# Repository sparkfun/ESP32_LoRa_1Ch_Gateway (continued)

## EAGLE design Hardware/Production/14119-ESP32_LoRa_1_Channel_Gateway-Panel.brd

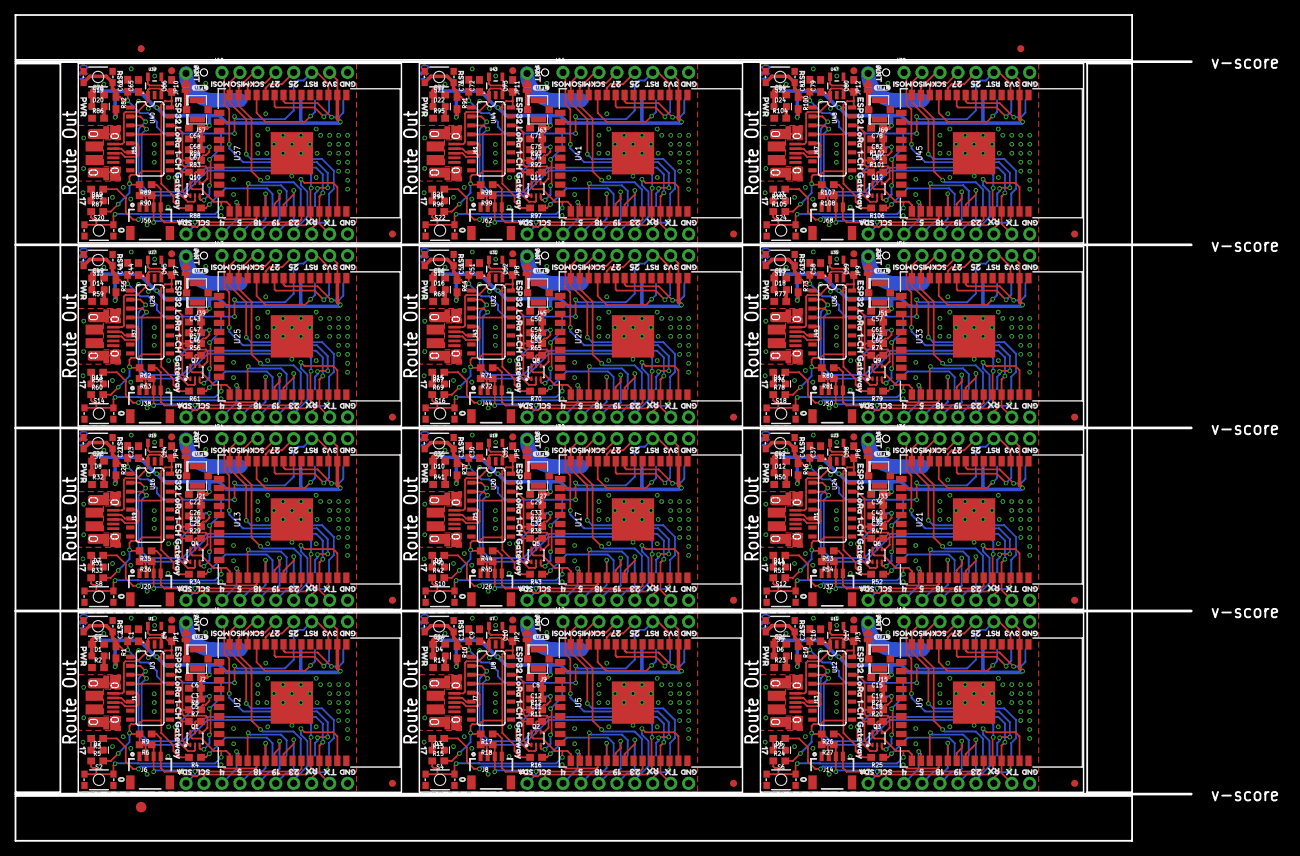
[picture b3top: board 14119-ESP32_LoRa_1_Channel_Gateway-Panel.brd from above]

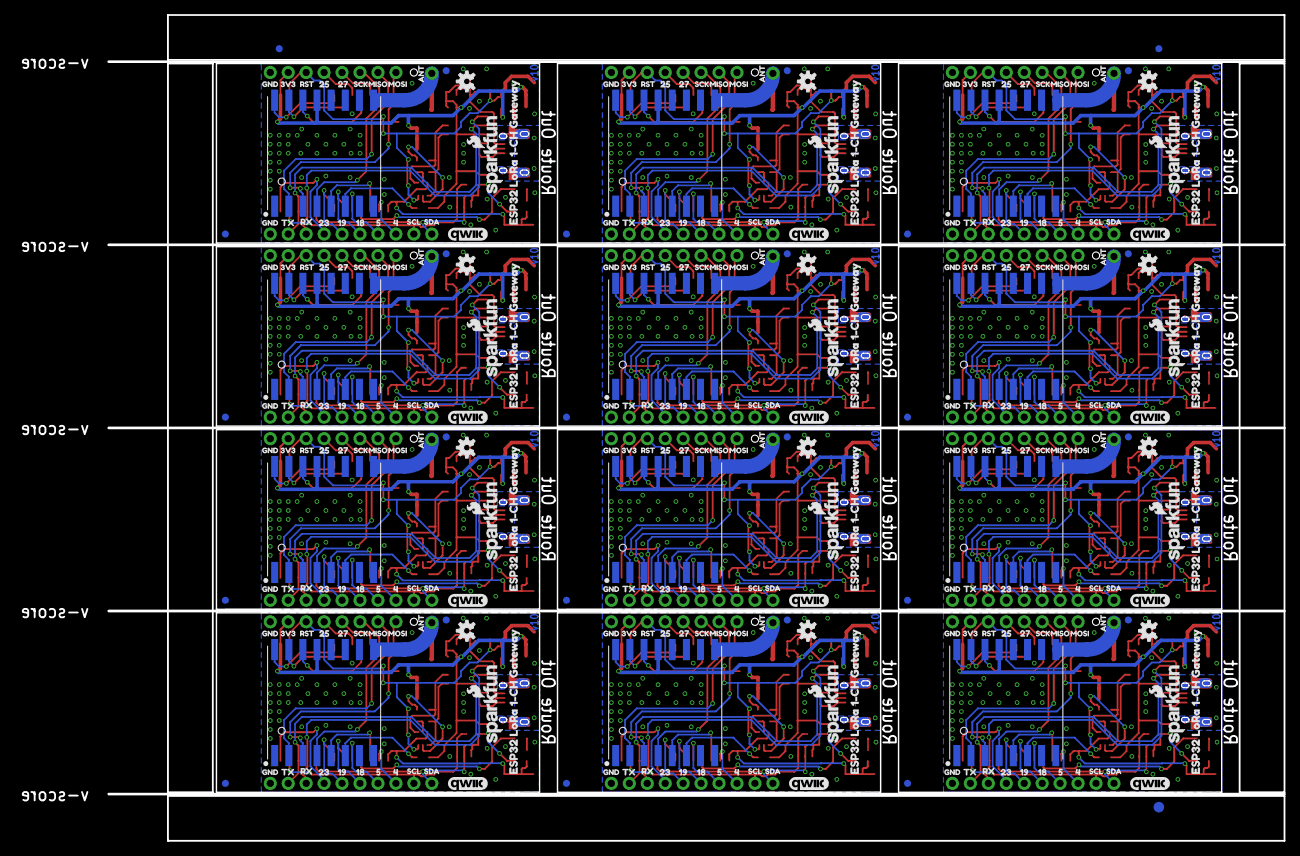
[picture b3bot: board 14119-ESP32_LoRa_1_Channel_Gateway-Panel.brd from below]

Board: 2 copper layers, 166.4 x 116.8 mm, 1014 parts (315 on the bottom side), 432 nets.

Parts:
C1, C4, C9, C10, C16, C17, C23, C24, C30, C31, C37, C38, C44, C45, C51, C52, C58, C59, C65, C66, C72, C73, C79, C80: 1.0uF; 0603
C2, C3, C7, C12, C13, C14, C19, C20, C21, C26, C27, C28, C33, C34, C35, C40, C41, C42, C47, C48, C49, C54, C55, C56, C61, C62, C63, C68, C69, C70, C75, C76, C77, C82, C83, C84: 0.1uF; 0603
C5, C11, C18, C25, C32, C39, C46, C53, C60, C67, C74, C81: 10uF; 0603
C6, C8, C15, C22, C29, C36, C43, C50, C57, C64, C71, C78: 4.7uF; 0603
D1, D4, D6, D8, D10, D12, D14, D16, D18, D20, D22, D24: RED; LED-0603
D2, D3, D5, D7, D9, D11, D13, D15, D17, D19, D21, D23: BLUE; LED-0603
E$1, E$2, E$3, E$4: FIDUCIAL-1X2
E$5, E$6: FIDUCIAL-1.5X3
FD1, FD2, FD3, FD4, FD5, FD6, FD7, FD8, FD9, FD10, FD11, FD12, FD13, FD14, FD15, FD16, FD17, FD18, FD19, FD20, FD21, FD22, FD23, FD24, FD25, FD26, FD27, FD28, FD29, FD30, FD31, FD32, FD33, FD34, FD35, FD36, FD37, FD38, FD39, FD40, FD41, FD42, FD43, FD44, FD45, FD46, FD47, FD48: FIDUCIAL1X2; FIDUCIAL-1X2
J1, J7, J13, J19, J25, J31, J37, J43, J49, J55, J61, J67: USB; USB-MICROB-PTH-MILL
J2, J9, J15, J21, J27, J33, J39, J45, J51, J57, J63, J69: U.FL
J3, J10, J16, J22, J28, J34, J40, J46, J52, J58, J64, J70: 1X01_NO_SILK
J4, J12, J18, J24, J30, J36, J42, J48, J54, J60, J66, J72: 1X08_NO_SILK
J5, J11, J17, J23, J29, J35, J41, J47, J53, J59, J65, J71: 1X10_NO_SILK
J6, J8, J14, J20, J26, J32, J38, J44, J50, J56, J62, J68: QWIIC; 1X04_1MM_RA
JP1, JP2, JP3, JP4, JP5, JP6, JP7, JP8, JP9, JP10, JP11, JP12: Ant Sel; SMT-JUMPER_2_NO_NO-SILK
LOGO1, LOGO3, LOGO5, LOGO7, LOGO9, LOGO11, LOGO13, LOGO15, LOGO17, LOGO19, LOGO21, LOGO23: OSHW-LOGOS; OSHW-LOGO-S
LOGO2, LOGO4, LOGO6, LOGO8, LOGO10, LOGO12, LOGO14, LOGO16, LOGO18, LOGO20, LOGO22, LOGO24: SFE_LOGO_NAME_FLAME.1_INCH; SFE_LOGO_NAME_FLAME_.1
Q1, Q2, Q3, Q4, Q5, Q6, Q7, Q8, Q9, Q10, Q11, Q12: MBT3904DW1T1; SC70-6
R1, R4, R5, R7, R8, R10, R11, R12, R15, R16, R19, R20, R21, R24, R25, R28, R29, R30, R33, R34, R37, R38, R39, R42, R43, R46, R47, R48, R51, R52, R55, R56, R57, R60, R61, R64, R65, R66, R69, R70, R73, R74, R75, R78, R79, R82, R83, R84, R87, R88, R91, R92, R93, R96, R97, R100, R101, R102, R105, R106: 10k; 0603
R2, R3, R13, R14, R22, R23, R31, R32, R40, R41, R49, R50, R58, R59, R67, R68, R76, R77, R85, R86, R94, R95, R103, R104: 1k; 0603
R6, R9, R17, R18, R26, R27, R35, R36, R44, R45, R53, R54, R62, R63, R71, R72, R80, R81, R89, R90, R98, R99, R107, R108: 2.2k; 0603
S1, S3, S5, S7, S9, S11, S13, S15, S17, S19, S21, S23: RESET; TACTILE_SWITCH_SMD_4.6X2.8MM
S2, S4, S6, S8, S10, S12, S14, S16, S18, S20, S22, S24: 0; TACTILE_SWITCH_SMD_4.6X2.8MM
U1, U7, U11, U15, U19, U23, U27, U31, U35, U39, U43, U47: 3.3V; SOT23-5
U2, U5, U9, U13, U17, U21, U25, U29, U33, U37, U41, U45: ESP-WROOM-32NARROW; ESP-WROOM-32-NARROW
U3, U8, U12, U16, U20, U24, U28, U32, U36, U40, U44, U48: CH340C; SO016
U4, U6, U10, U14, U18, U22, U26, U30, U34, U38, U42, U46: RFM95W; RFM95/96/97/98W
U$1, U$10, U$26, U$37, U$48, U$56, U$71, U$82, U$94, U$102, U$117, U$128, U$140, U$148, U$163, U$174, U$186, U$194, U$209, U$220, U$232, U$240, U$255, U$266, U$278, U$286, U$301, U$312, U$324, U$332, U$347, U$358, U$370, U$378, U$393, U$404, U$416, U$424, U$439, U$450, U$462, U$470, U$485, U$496, U$508, U$516, U$531, U$542: GND0
U$2, U$38, U$49, U$83, U$95, U$129, U$141, U$175, U$187, U$221, U$233, U$267, U$279, U$313, U$325, U$359, U$371, U$405, U$417, U$451, U$463, U$497, U$509, U$543: 3V31
U$3, U$20, U$39, U$50, U$66, U$84, U$96, U$112, U$130, U$142, U$158, U$176, U$188, U$204, U$222, U$234, U$250, U$268, U$280, U$296, U$314, U$326, U$342, U$360, U$372, U$388, U$406, U$418, U$434, U$452, U$464, U$480, U$498, U$510, U$526, U$544: RST2
U$4, U$40, U$51, U$85, U$97, U$131, U$143, U$177, U$189, U$223, U$235, U$269, U$281, U$315, U$327, U$361, U$373, U$407, U$419, U$453, U$465, U$499, U$511, U$545: 2517
U$5, U$41, U$52, U$86, U$98, U$132, U$144, U$178, U$190, U$224, U$236, U$270, U$282, U$316, U$328, U$362, U$374, U$408, U$420, U$454, U$466, U$500, U$512, U$546: 279
U$6, U$42, U$53, U$87, U$99, U$133, U$145, U$179, U$191, U$225, U$237, U$271, U$283, U$317, U$329, U$363, U$375, U$409, U$421, U$455, U$467, U$501, U$513, U$547: SCK3
U$7, U$43, U$54, U$88, U$100, U$134, U$146, U$180, U$192, U$226, U$238, U$272, U$284, U$318, U$330, U$364, U$376, U$410, U$422, U$456, U$468, U$502, U$514, U$548: MISO4
U$8, U$44, U$55, U$89, U$101, U$135, U$147, U$181, U$193, U$227, U$239, U$273, U$285, U$319, U$331, U$365, U$377, U$411, U$423, U$457, U$469, U$503, U$515, U$549: MOSI5
U$9, U$36, U$47, U$81, U$93, U$127, U$139, U$173, U$185, U$219, U$231, U$265, U$277, U$311, U$323, U$357, U$369, U$403, U$415, U$449, U$461, U$495, U$507, U$541: ANT6
U$11, U$27, U$57, U$72, U$103, U$118, U$149, U$164, U$195, U$210, U$241, U$256, U$287, U$302, U$333, U$348, U$379, U$394, U$425, U$440, U$471, U$486, U$517, U$532: TX16
U$12, U$28, U$58, U$73, U$104, U$119, U$150, U$165, U$196, U$211, U$242, U$257, U$288, U$303, U$334, U$349, U$380, U$395, U$426, U$441, U$472, U$487, U$518, U$533: RX15
U$13, U$29, U$59, U$74, U$105, U$120, U$151, U$166, U$197, U$212, U$243, U$258, U$289, U$304, U$335, U$350, U$381, U$396, U$427, U$442, U$473, U$488, U$519, U$534: 2314
U$14, U$30, U$60, U$75, U$106, U$121, U$152, U$167, U$198, U$213, U$244, U$259, U$290, U$305, U$336, U$351, U$382, U$397, U$428, U$443, U$474, U$489, U$520, U$535: 1912
U$15, U$31, U$61, U$76, U$107, U$122, U$153, U$168, U$199, U$214, U$245, U$260, U$291, U$306, U$337, U$352, U$383, U$398, U$429, U$444, U$475, U$490, U$521, U$536: 1811
U$16, U$32, U$62, U$77, U$108, U$123, U$154, U$169, U$200, U$215, U$246, U$261, U$292, U$307, U$338, U$353, U$384, U$399, U$430, U$445, U$476, U$491, U$522, U$537: 513
U$17, U$33, U$63, U$78, U$109, U$124, U$155, U$170, U$201, U$216, U$247, U$262, U$293, U$308, U$339, U$354, U$385, U$400, U$431, U$446, U$477, U$492, U$523, U$538: 410
U$18, U$34, U$64, U$79, U$110, U$125, U$156, U$171, U$202, U$217, U$248, U$263, U$294, U$309, U$340, U$355, U$386, U$401, U$432, U$447, U$478, U$493, U$524, U$539: SCL8
U$19, U$35, U$65, U$80, U$111, U$126, U$157, U$172, U$203, U$218, U$249, U$264, U$295, U$310, U$341, U$356, U$387, U$402, U$433, U$448, U$479, U$494, U$525, U$540: SDA7
U$21, U$67, U$113, U$159, U$205, U$251, U$297, U$343, U$389, U$435, U$481, U$527: 020
U$22, U$68, U$114, U$160, U$206, U$252, U$298, U$344, U$390, U$436, U$482, U$528: PWR19
U$23, U$69, U$115, U$161, U$207, U$253, U$299, U$345, U$391, U$437, U$483, U$529: 1722
U$24, U$92, U$138, U$184, U$230, U$276, U$322, U$368, U$414, U$460, U$506, U$552: U#FL0
U$25, U$70, U$116, U$162, U$208, U$254, U$300, U$346, U$392, U$438, U$484, U$530: ESP32_LORA_1#CH_GATEWAY21
U$45, U$90, U$136, U$182, U$228, U$274, U$320, U$366, U$412, U$458, U$504, U$550: ESP32_LORA_1#CH_GATEWAY23
U$46, U$91, U$137, U$183, U$229, U$275, U$321, U$367, U$413, U$459, U$505, U$551: QWIIC_COPYRIGHT_SMALL

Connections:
0: Q1.6, R5.1, S2.3, S2.4, U2.25
1: Q2.6, R15.1, S4.3, S4.4, U5.25
2: Q3.6, R24.1, S6.3, S6.4, U9.25
3: Q4.6, R33.1, S8.3, S8.4, U13.25
3.3V: C3.1, C4.1, C5.1, C6.1, C7.1, D1.A, J4.7, J6.2, R1.2, R4.2, R5.2, R6.2, R9.2, U1.5, U2.2, U3.4, U3.16, U4.3.3V
3.3V1: C8.1, C10.1, C11.1, C12.1, C14.1, D4.A, J8.2, J12.7, R10.2, R15.2, R16.2, R17.2, R18.2, U5.2, U6.3.3V, U7.5, U8.4, U8.16
3.3V2: C15.1, C17.1, C18.1, C19.1, C21.1, D6.A, J14.2, J18.7, R19.2, R24.2, R25.2, R26.2, R27.2, U9.2, U10.3.3V, U11.5, U12.4, U12.16
3.3V3: C22.1, C24.1, C25.1, C26.1, C28.1, D8.A, J20.2, J24.7, R28.2, R33.2, R34.2, R35.2, R36.2, U13.2, U14.3.3V, U15.5, U16.4, U16.16
3.3V4: C29.1, C31.1, C32.1, C33.1, C35.1, D10.A, J26.2, J30.7, R37.2, R42.2, R43.2, R44.2, R45.2, U17.2, U18.3.3V, U19.5, U20.4, U20.16
3.3V5: C36.1, C38.1, C39.1, C40.1, C42.1, D12.A, J32.2, J36.7, R46.2, R51.2, R52.2, R53.2, R54.2, U21.2, U22.3.3V, U23.5, U24.4, U24.16
3.3V6: C43.1, C45.1, C46.1, C47.1, C49.1, D14.A, J38.2, J42.7, R55.2, R60.2, R61.2, R62.2, R63.2, U25.2, U26.3.3V, U27.5, U28.4, U28.16
3.3V7: C50.1, C52.1, C53.1, C54.1, C56.1, D16.A, J44.2, J48.7, R64.2, R69.2, R70.2, R71.2, R72.2, U29.2, U30.3.3V, U31.5, U32.4, U32.16
3.3V8: C57.1, C59.1, C60.1, C61.1, C63.1, D18.A, J50.2, J54.7, R73.2, R78.2, R79.2, R80.2, R81.2, U33.2, U34.3.3V, U35.5, U36.4, U36.16
3.3V9: C64.1, C66.1, C67.1, C68.1, C70.1, D20.A, J56.2, J60.7, R82.2, R87.2, R88.2, R89.2, R90.2, U37.2, U38.3.3V, U39.5, U40.4, U40.16
3.3V10: C71.1, C73.1, C74.1, C75.1, C77.1, D22.A, J62.2, J66.7, R91.2, R96.2, R97.2, R98.2, R99.2, U41.2, U42.3.3V, U43.5, U44.4, U44.16
3.3V11: C78.1, C80.1, C81.1, C82.1, C84.1, D24.A, J68.2, J72.7, R100.2, R105.2, R106.2, R107.2, R108.2, U45.2, U46.3.3V, U47.5, U48.4, U48.16
4: Q5.6, R42.1, S10.3, S10.4, U17.25
5: Q6.6, R51.1, S12.3, S12.4, U21.25
6: Q7.6, R60.1, S14.3, S14.4, U25.25
7: Q8.6, R69.1, S16.3, S16.4, U29.25
8: Q9.6, R78.1, S18.3, S18.4, U33.25
9: Q10.6, R87.1, S20.3, S20.4, U37.25
10: Q11.6, R96.1, S22.3, S22.4, U41.25
11: Q12.6, R105.1, S24.3, S24.4, U45.25
!DTR: Q1.1, R7.1, U3.13
!DTR1: Q2.1, R11.1, U8.13
!DTR2: Q3.1, R20.1, U12.13
!DTR3: Q4.1, R29.1, U16.13
!DTR4: Q5.1, R38.1, U20.13
!DTR5: Q6.1, R47.1, U24.13
!DTR6: Q7.1, R56.1, U28.13
!DTR7: Q8.1, R65.1, U32.13
!DTR8: Q9.1, R74.1, U36.13
!DTR9: Q10.1, R83.1, U40.13
!DTR10: Q11.1, R92.1, U44.13
!DTR11: Q12.1, R101.1, U48.13
!RTS: Q1.4, R8.1, U3.14
!RTS1: Q2.4, R12.1, U8.14
!RTS2: Q3.4, R21.1, U12.14
!RTS3: Q4.4, R30.1, U16.14
!RTS4: Q5.4, R39.1, U20.14
!RTS5: Q6.4, R48.1, U24.14
!RTS6: Q7.4, R57.1, U28.14
!RTS7: Q8.4, R66.1, U32.14
!RTS8: Q9.4, R75.1, U36.14
!RTS9: Q10.4, R84.1, U40.14
!RTS10: Q11.4, R93.1, U44.14
!RTS11: Q12.4, R102.1, U48.14
ANT: J3.1, JP1.2, U4.ANT
ANT1: J10.1, JP2.2, U6.ANT
ANT2: J16.1, JP3.2, U10.ANT
ANT3: J22.1, JP4.2, U14.ANT
ANT4: J28.1, JP5.2, U18.ANT
ANT5: J34.1, JP6.2, U22.ANT
ANT6: J40.1, JP7.2, U26.ANT
ANT7: J46.1, JP8.2, U30.ANT
ANT8: J52.1, JP9.2, U34.ANT
ANT9: J58.1, JP10.2, U38.ANT
ANT10: J64.1, JP11.2, U42.ANT
ANT11: J70.1, JP12.2, U46.ANT
D+: J1.D+, U3.5
D+1: J7.D+, U8.5
D+2: J13.D+, U12.5
D+3: J19.D+, U16.5
D+4: J25.D+, U20.5
D+5: J31.D+, U24.5
D+6: J37.D+, U28.5
D+7: J43.D+, U32.5
D+8: J49.D+, U36.5
D+9: J55.D+, U40.5
D+10: J61.D+, U44.5
D+11: J67.D+, U48.5
D-: J1.D-, U3.6
D-1: J7.D-, U8.6
D-2: J13.D-, U12.6
D-3: J19.D-, U16.6
D-4: J25.D-, U20.6
D-5: J31.D-, U24.6
D-6: J37.D-, U28.6
D-7: J43.D-, U32.6
D-8: J49.D-, U36.6
D-9: J55.D-, U40.6
D-10: J61.D-, U44.6
D-11: J67.D-, U48.6
GND: C1.2, C2.2, C3.2, C4.2, C5.2, C6.2, C7.2, D2.C, J1.GND, J2.1, J2.2, J4.8, J5.10, J6.1, R2.1, S1.1, S1.2, S2.1, S2.2, U1.2, U2.1, U2.15, U2.38, U2.GND, U3.1, U4.GND@1, U4.GND@2, U4.GND@3
GND1: C8.2, C9.2, C10.2, C11.2, C12.2, C13.2, C14.2, D3.C, J7.GND, J8.1, J9.1, J9.2, J11.10, J12.8, R14.1, S3.1, S3.2, S4.1, S4.2, U5.1, U5.15, U5.38, U5.GND, U6.GND@1, U6.GND@2, U6.GND@3, U7.2, U8.1
GND2: C15.2, C16.2, C17.2, C18.2, C19.2, C20.2, C21.2, D5.C, J13.GND, J14.1, J15.1, J15.2, J17.10, J18.8, R23.1, S5.1, S5.2, S6.1, S6.2, U9.1, U9.15, U9.38, U9.GND, U10.GND@1, U10.GND@2, U10.GND@3, U11.2, U12.1
GND3: C22.2, C23.2, C24.2, C25.2, C26.2, C27.2, C28.2, D7.C, J19.GND, J20.1, J21.1, J21.2, J23.10, J24.8, R32.1, S7.1, S7.2, S8.1, S8.2, U13.1, U13.15, U13.38, U13.GND, U14.GND@1, U14.GND@2, U14.GND@3, U15.2, U16.1
GND4: C29.2, C30.2, C31.2, C32.2, C33.2, C34.2, C35.2, D9.C, J25.GND, J26.1, J27.1, J27.2, J29.10, J30.8, R41.1, S9.1, S9.2, S10.1, S10.2, U17.1, U17.15, U17.38, U17.GND, U18.GND@1, U18.GND@2, U18.GND@3, U19.2, U20.1
GND5: C36.2, C37.2, C38.2, C39.2, C40.2, C41.2, C42.2, D11.C, J31.GND, J32.1, J33.1, J33.2, J35.10, J36.8, R50.1, S11.1, S11.2, S12.1, S12.2, U21.1, U21.15, U21.38, U21.GND, U22.GND@1, U22.GND@2, U22.GND@3, U23.2, U24.1
GND6: C43.2, C44.2, C45.2, C46.2, C47.2, C48.2, C49.2, D13.C, J37.GND, J38.1, J39.1, J39.2, J41.10, J42.8, R59.1, S13.1, S13.2, S14.1, S14.2, U25.1, U25.15, U25.38, U25.GND, U26.GND@1, U26.GND@2, U26.GND@3, U27.2, U28.1
GND7: C50.2, C51.2, C52.2, C53.2, C54.2, C55.2, C56.2, D15.C, J43.GND, J44.1, J45.1, J45.2, J47.10, J48.8, R68.1, S15.1, S15.2, S16.1, S16.2, U29.1, U29.15, U29.38, U29.GND, U30.GND@1, U30.GND@2, U30.GND@3, U31.2, U32.1
GND8: C57.2, C58.2, C59.2, C60.2, C61.2, C62.2, C63.2, D17.C, J49.GND, J50.1, J51.1, J51.2, J53.10, J54.8, R77.1, S17.1, S17.2, S18.1, S18.2, U33.1, U33.15, U33.38, U33.GND, U34.GND@1, U34.GND@2, U34.GND@3, U35.2, U36.1
GND9: C64.2, C65.2, C66.2, C67.2, C68.2, C69.2, C70.2, D19.C, J55.GND, J56.1, J57.1, J57.2, J59.10, J60.8, R86.1, S19.1, S19.2, S20.1, S20.2, U37.1, U37.15, U37.38, U37.GND, U38.GND@1, U38.GND@2, U38.GND@3, U39.2, U40.1
GND10: C71.2, C72.2, C73.2, C74.2, C75.2, C76.2, C77.2, D21.C, J61.GND, J62.1, J63.1, J63.2, J65.10, J66.8, R95.1, S21.1, S21.2, S22.1, S22.2, U41.1, U41.15, U41.38, U41.GND, U42.GND@1, U42.GND@2, U42.GND@3, U43.2, U44.1
GND11: C78.2, C79.2, C80.2, C81.2, C82.2, C83.2, C84.2, D23.C, J67.GND, J68.1, J69.1, J69.2, J71.10, J72.8, R104.1, S23.1, S23.2, S24.1, S24.2, U45.1, U45.15, U45.38, U45.GND, U46.GND@1, U46.GND@2, U46.GND@3, U47.2, U48.1
IO1: J12.5, U5.10
IO2: J12.4, U5.12
IO3: J11.6, U5.31
IO4: J5.3, U2.26
IO5: J5.4, U2.29
IO6: J11.5, U5.30
IO7: J11.4, U5.29
IO8: J11.7, U5.37
IO9: J11.3, U5.26
IO10: R13.1, U5.28
IO11: J18.5, U9.10
IO12: J18.4, U9.12
IO13: J17.6, U9.31
IO14: J17.5, U9.30
IO15: J17.4, U9.29
IO16: J17.7, U9.37
IO17: R3.1, U2.28
IO18: J5.5, U2.30
IO19: J5.6, U2.31
IO20: J17.3, U9.26
IO21: R22.1, U9.28
IO22: J24.5, U13.10
IO23: J5.7, U2.37
IO24: J24.4, U13.12
IO25: J4.5, U2.10
IO26: J23.6, U13.31
IO27: J4.4, U2.12
IO28: J23.5, U13.30
IO29: J23.4, U13.29
IO30: J23.7, U13.37
IO31: J23.3, U13.26
IO32: R31.1, U13.28
IO33: J30.5, U17.10
IO34: J30.4, U17.12
IO35: J29.6, U17.31
IO36: J29.5, U17.30
IO37: J29.4, U17.29
IO38: J29.7, U17.37
IO39: J29.3, U17.26
IO40: R40.1, U17.28
IO41: J36.5, U21.10
IO42: J36.4, U21.12
IO43: J35.6, U21.31
IO44: J35.5, U21.30
IO45: J35.4, U21.29
IO46: J35.7, U21.37
IO47: J35.3, U21.26
IO48: R49.1, U21.28
IO49: J42.5, U25.10
IO50: J42.4, U25.12
IO51: J41.6, U25.31
IO52: J41.5, U25.30
IO53: J41.4, U25.29
IO54: J41.7, U25.37
IO55: J41.3, U25.26
IO56: R58.1, U25.28
IO57: J48.5, U29.10
IO58: J48.4, U29.12
IO59: J47.6, U29.31
IO60: J47.5, U29.30
IO61: J47.4, U29.29
IO62: J47.7, U29.37
IO63: J47.3, U29.26
IO64: R67.1, U29.28
IO65: J54.5, U33.10
IO66: J54.4, U33.12
IO67: J53.6, U33.31
IO68: J53.5, U33.30
IO69: J53.4, U33.29
IO70: J53.7, U33.37
IO71: J53.3, U33.26
IO72: R76.1, U33.28
IO73: J60.5, U37.10
IO74: J60.4, U37.12
IO75: J59.6, U37.31
IO76: J59.5, U37.30
IO77: J59.4, U37.29
IO78: J59.7, U37.37
IO79: J59.3, U37.26
IO80: R85.1, U37.28
IO81: J66.5, U41.10
IO82: J66.4, U41.12
IO83: J65.6, U41.31
IO84: J65.5, U41.30
IO85: J65.4, U41.29
IO86: J65.7, U41.37
IO87: J65.3, U41.26
IO88: R94.1, U41.28
IO89: J72.5, U45.10
IO90: J72.4, U45.12
IO91: J71.6, U45.31
IO92: J71.5, U45.30
IO93: J71.4, U45.29
IO94: J71.7, U45.37
IO95: J71.3, U45.26
IO96: R103.1, U45.28
MISO: J4.2, U2.14, U4.MISO
MISO1: J12.2, U5.14, U6.MISO
MISO2: J18.2, U9.14, U10.MISO
MISO3: J24.2, U13.14, U14.MISO
MISO4: J30.2, U17.14, U18.MISO
MISO5: J36.2, U21.14, U22.MISO
MISO6: J42.2, U25.14, U26.MISO
MISO7: J48.2, U29.14, U30.MISO
MISO8: J54.2, U33.14, U34.MISO
MISO9: J60.2, U37.14, U38.MISO
MISO10: J66.2, U41.14, U42.MISO
MISO11: J72.2, U45.14, U46.MISO
MOSI: J4.1, U2.16, U4.MOSI
MOSI1: J12.1, U5.16, U6.MOSI
MOSI2: J18.1, U9.16, U10.MOSI
MOSI3: J24.1, U13.16, U14.MOSI
MOSI4: J30.1, U17.16, U18.MOSI
MOSI5: J36.1, U21.16, U22.MOSI
MOSI6: J42.1, U25.16, U26.MOSI
MOSI7: J48.1, U29.16, U30.MOSI
MOSI8: J54.1, U33.16, U34.MOSI
MOSI9: J60.1, U37.16, U38.MOSI
MOSI10: J66.1, U41.16, U42.MOSI
MOSI11: J72.1, U45.16, U46.MOSI
unnamed: D1.C, R2.2
unnamed: D2.A, R3.2
unnamed: J2.FEED, JP1.1
unnamed: Q2.5, R11.2
unnamed: Q2.2, R12.2
unnamed: D3.A, R13.2
unnamed: D4.C, R14.2
unnamed: J9.FEED, JP2.1
unnamed: Q3.5, R20.2
unnamed: Q1.5, R7.2
unnamed: Q3.2, R21.2
unnamed: Q1.2, R8.2
unnamed: D5.A, R22.2
unnamed: D6.C, R23.2
unnamed: J15.FEED, JP3.1
unnamed: Q4.5, R29.2
unnamed: Q4.2, R30.2
unnamed: D7.A, R31.2
unnamed: D8.C, R32.2
unnamed: J21.FEED, JP4.1
unnamed: Q5.5, R38.2
unnamed: Q5.2, R39.2
unnamed: D9.A, R40.2
unnamed: D10.C, R41.2
unnamed: J27.FEED, JP5.1
unnamed: Q6.5, R47.2
unnamed: Q6.2, R48.2
unnamed: D11.A, R49.2
unnamed: D12.C, R50.2
unnamed: J33.FEED, JP6.1
unnamed: Q7.5, R56.2
unnamed: Q7.2, R57.2
unnamed: D13.A, R58.2
unnamed: D14.C, R59.2
unnamed: J39.FEED, JP7.1
unnamed: Q8.5, R65.2
unnamed: Q8.2, R66.2
unnamed: D15.A, R67.2
unnamed: D16.C, R68.2
unnamed: J45.FEED, JP8.1
unnamed: Q9.5, R74.2
unnamed: Q9.2, R75.2
unnamed: D17.A, R76.2
unnamed: D18.C, R77.2
unnamed: J51.FEED, JP9.1
unnamed: Q10.5, R83.2
unnamed: Q10.2, R84.2
unnamed: D19.A, R85.2
unnamed: D20.C, R86.2
unnamed: J57.FEED, JP10.1
unnamed: Q11.5, R92.2
unnamed: Q11.2, R93.2
unnamed: D21.A, R94.2
unnamed: D22.C, R95.2
unnamed: J63.FEED, JP11.1
unnamed: Q12.5, R101.2
unnamed: Q12.2, R102.2
unnamed: D23.A, R103.2
unnamed: D24.C, R104.2
unnamed: J69.FEED, JP12.1
RESET: C2.1, J4.6, Q1.3, R1.1, S1.3, S1.4, U2.3
RESET1: C13.1, J12.6, Q2.3, R10.1, S3.3, S3.4, U5.3
RESET2: C20.1, J18.6, Q3.3, R19.1, S5.3, S5.4, U9.3
RESET3: C27.1, J24.6, Q4.3, R28.1, S7.3, S7.4, U13.3
RESET4: C34.1, J30.6, Q5.3, R37.1, S9.3, S9.4, U17.3
RESET5: C41.1, J36.6, Q6.3, R46.1, S11.3, S11.4, U21.3
RESET6: C48.1, J42.6, Q7.3, R55.1, S13.3, S13.4, U25.3
RESET7: C55.1, J48.6, Q8.3, R64.1, S15.3, S15.4, U29.3
RESET8: C62.1, J54.6, Q9.3, R73.1, S17.3, S17.4, U33.3
RESET9: C69.1, J60.6, Q10.3, R82.1, S19.3, S19.4, U37.3
RESET10: C76.1, J66.6, Q11.3, R91.1, S21.3, S21.4, U41.3
RESET11: C83.1, J72.6, Q12.3, R100.1, S23.3, S23.4, U45.3
RFM_CS: U2.27, U4.NSS
RFM_CS1: U5.27, U6.NSS
RFM_CS2: U9.27, U10.NSS
RFM_CS3: U13.27, U14.NSS
RFM_CS4: U17.27, U18.NSS
RFM_CS5: U21.27, U22.NSS
RFM_CS6: U25.27, U26.NSS
RFM_CS7: U29.27, U30.NSS
RFM_CS8: U33.27, U34.NSS
RFM_CS9: U37.27, U38.NSS
RFM_CS10: U41.27, U42.NSS
RFM_CS11: U45.27, U46.NSS
RFM_DIO1/1: U5.9, U6.DIO1
RFM_DIO1/2: U9.9, U10.DIO1
RFM_DIO1/3: U13.9, U14.DIO1
RFM_DIO1/4: U17.9, U18.DIO1
RFM_DIO1/5: U21.9, U22.DIO1
RFM_DIO1/6: U25.9, U26.DIO1
RFM_DIO1/7: U29.9, U30.DIO1
RFM_DIO1/8: U33.9, U34.DIO1
RFM_DIO1/9: U37.9, U38.DIO1
RFM_DIO1/10: U41.9, U42.DIO1
RFM_DIO1/11: U45.9, U46.DIO1
RFM_DIO1/33: U2.9, U4.DIO1
RFM_DIO2/1: U5.8, U6.DIO2
RFM_DIO2/2: U9.8, U10.DIO2
RFM_DIO2/3: U13.8, U14.DIO2
RFM_DIO2/4: U17.8, U18.DIO2
RFM_DIO2/5: U21.8, U22.DIO2
RFM_DIO2/6: U25.8, U26.DIO2
RFM_DIO2/7: U29.8, U30.DIO2
RFM_DIO2/8: U33.8, U34.DIO2
RFM_DIO2/9: U37.8, U38.DIO2
RFM_DIO2/10: U41.8, U42.DIO2
RFM_DIO2/11: U45.8, U46.DIO2
RFM_DIO2/32: U2.8, U4.DIO2
RFM_INT/1: U5.11, U6.DIO0
RFM_INT/2: U9.11, U10.DIO0
RFM_INT/3: U13.11, U14.DIO0
RFM_INT/4: U17.11, U18.DIO0
RFM_INT/5: U21.11, U22.DIO0
RFM_INT/6: U25.11, U26.DIO0
RFM_INT/7: U29.11, U30.DIO0
RFM_INT/8: U33.11, U34.DIO0
RFM_INT/9: U37.11, U38.DIO0
RFM_INT/10: U41.11, U42.DIO0
RFM_INT/11: U45.11, U46.DIO0
RFM_INT/26: U2.11, U4.DIO0
RFM_RST: R4.1, U4.!RESET
RFM_RST1: R16.1, U6.!RESET
RFM_RST2: R25.1, U10.!RESET
RFM_RST3: R34.1, U14.!RESET
RFM_RST4: R43.1, U18.!RESET
RFM_RST5: R52.1, U22.!RESET
RFM_RST6: R61.1, U26.!RESET
RFM_RST7: R70.1, U30.!RESET
RFM_RST8: R79.1, U34.!RESET
RFM_RST9: R88.1, U38.!RESET
RFM_RST10: R97.1, U42.!RESET
RFM_RST11: R106.1, U46.!RESET
RXI: J5.8, U2.34, U3.2
RXI1: J11.8, U5.34, U8.2
RXI2: J17.8, U9.34, U12.2
RXI3: J23.8, U13.34, U16.2
RXI4: J29.8, U17.34, U20.2
RXI5: J35.8, U21.34, U24.2
RXI6: J41.8, U25.34, U28.2
RXI7: J47.8, U29.34, U32.2
RXI8: J53.8, U33.34, U36.2
RXI9: J59.8, U37.34, U40.2
RXI10: J65.8, U41.34, U44.2
RXI11: J71.8, U45.34, U48.2
SCK: J4.3, U2.13, U4.SCK
SCK1: J12.3, U5.13, U6.SCK
SCK2: J18.3, U9.13, U10.SCK
SCK3: J24.3, U13.13, U14.SCK
SCK4: J30.3, U17.13, U18.SCK
SCK5: J36.3, U21.13, U22.SCK
SCK6: J42.3, U25.13, U26.SCK
SCK7: J48.3, U29.13, U30.SCK
SCK8: J54.3, U33.13, U34.SCK
SCK9: J60.3, U37.13, U38.SCK
SCK10: J66.3, U41.13, U42.SCK
SCK11: J72.3, U45.13, U46.SCK
SCL: J5.2, J6.4, R9.1, U2.36
SCL1: J8.4, J11.2, R17.1, U5.36
SCL2: J14.4, J17.2, R26.1, U9.36
SCL3: J20.4, J23.2, R35.1, U13.36
SCL4: J26.4, J29.2, R44.1, U17.36
SCL5: J32.4, J35.2, R53.1, U21.36
SCL6: J38.4, J41.2, R62.1, U25.36
SCL7: J44.4, J47.2, R71.1, U29.36
SCL8: J50.4, J53.2, R80.1, U33.36
SCL9: J56.4, J59.2, R89.1, U37.36
SCL10: J62.4, J65.2, R98.1, U41.36
SCL11: J68.4, J71.2, R107.1, U45.36
SDA: J5.1, J6.3, R6.1, U2.33
SDA1: J8.3, J11.1, R18.1, U5.33
SDA2: J14.3, J17.1, R27.1, U9.33
SDA3: J20.3, J23.1, R36.1, U13.33
SDA4: J26.3, J29.1, R45.1, U17.33
SDA5: J32.3, J35.1, R54.1, U21.33
SDA6: J38.3, J41.1, R63.1, U25.33
SDA7: J44.3, J47.1, R72.1, U29.33
SDA8: J50.3, J53.1, R81.1, U33.33
SDA9: J56.3, J59.1, R90.1, U37.33
SDA10: J62.3, J65.1, R99.1, U41.33
SDA11: J68.3, J71.1, R108.1, U45.33
SHIELD: J1.SHIELD, J1.SHIELD2, J1.SHIELD3, J1.SHIELD4, J1.SHIELD5, J1.SHIELD6, J1.SHIELD7, J1.SHIELD8, J1.SHIELD9, J1.SHIELD10
SHIELD1: J7.SHIELD, J7.SHIELD2, J7.SHIELD3, J7.SHIELD4, J7.SHIELD5, J7.SHIELD6, J7.SHIELD7, J7.SHIELD8, J7.SHIELD9, J7.SHIELD10
SHIELD2: J13.SHIELD, J13.SHIELD2, J13.SHIELD3, J13.SHIELD4, J13.SHIELD5, J13.SHIELD6, J13.SHIELD7, J13.SHIELD8, J13.SHIELD9, J13.SHIELD10
SHIELD3: J19.SHIELD, J19.SHIELD2, J19.SHIELD3, J19.SHIELD4, J19.SHIELD5, J19.SHIELD6, J19.SHIELD7, J19.SHIELD8, J19.SHIELD9, J19.SHIELD10
SHIELD4: J25.SHIELD, J25.SHIELD2, J25.SHIELD3, J25.SHIELD4, J25.SHIELD5, J25.SHIELD6, J25.SHIELD7, J25.SHIELD8, J25.SHIELD9, J25.SHIELD10
SHIELD5: J31.SHIELD, J31.SHIELD2, J31.SHIELD3, J31.SHIELD4, J31.SHIELD5, J31.SHIELD6, J31.SHIELD7, J31.SHIELD8, J31.SHIELD9, J31.SHIELD10
SHIELD6: J37.SHIELD, J37.SHIELD2, J37.SHIELD3, J37.SHIELD4, J37.SHIELD5, J37.SHIELD6, J37.SHIELD7, J37.SHIELD8, J37.SHIELD9, J37.SHIELD10
SHIELD7: J43.SHIELD, J43.SHIELD2, J43.SHIELD3, J43.SHIELD4, J43.SHIELD5, J43.SHIELD6, J43.SHIELD7, J43.SHIELD8, J43.SHIELD9, J43.SHIELD10
SHIELD8: J49.SHIELD, J49.SHIELD2, J49.SHIELD3, J49.SHIELD4, J49.SHIELD5, J49.SHIELD6, J49.SHIELD7, J49.SHIELD8, J49.SHIELD9, J49.SHIELD10
SHIELD9: J55.SHIELD, J55.SHIELD2, J55.SHIELD3, J55.SHIELD4, J55.SHIELD5, J55.SHIELD6, J55.SHIELD7, J55.SHIELD8, J55.SHIELD9, J55.SHIELD10
SHIELD10: J61.SHIELD, J61.SHIELD2, J61.SHIELD3, J61.SHIELD4, J61.SHIELD5, J61.SHIELD6, J61.SHIELD7, J61.SHIELD8, J61.SHIELD9, J61.SHIELD10
SHIELD11: J67.SHIELD, J67.SHIELD2, J67.SHIELD3, J67.SHIELD4, J67.SHIELD5, J67.SHIELD6, J67.SHIELD7, J67.SHIELD8, J67.SHIELD9, J67.SHIELD10
TXO: J5.9, U2.35, U3.3
TXO1: J11.9, U5.35, U8.3
TXO2: J17.9, U9.35, U12.3
TXO3: J23.9, U13.35, U16.3
TXO4: J29.9, U17.35, U20.3
TXO5: J35.9, U21.35, U24.3
TXO6: J41.9, U25.35, U28.3
TXO7: J47.9, U29.35, U32.3
TXO8: J53.9, U33.35, U36.3
TXO9: J59.9, U37.35, U40.3
TXO10: J65.9, U41.35, U44.3
TXO11: J71.9, U45.35, U48.3
V_USB: C1.1, J1.VBUS, U1.1, U1.3
V_USB1: C9.1, J7.VBUS, U7.1, U7.3
V_USB2: C16.1, J13.VBUS, U11.1, U11.3
V_USB3: C23.1, J19.VBUS, U15.1, U15.3
V_USB4: C30.1, J25.VBUS, U19.1, U19.3
V_USB5: C37.1, J31.VBUS, U23.1, U23.3
V_USB6: C44.1, J37.VBUS, U27.1, U27.3
V_USB7: C51.1, J43.VBUS, U31.1, U31.3
V_USB8: C58.1, J49.VBUS, U35.1, U35.3
V_USB9: C65.1, J55.VBUS, U39.1, U39.3
V_USB10: C72.1, J61.VBUS, U43.1, U43.3
V_USB11: C79.1, J67.VBUS, U47.1, U47.3
